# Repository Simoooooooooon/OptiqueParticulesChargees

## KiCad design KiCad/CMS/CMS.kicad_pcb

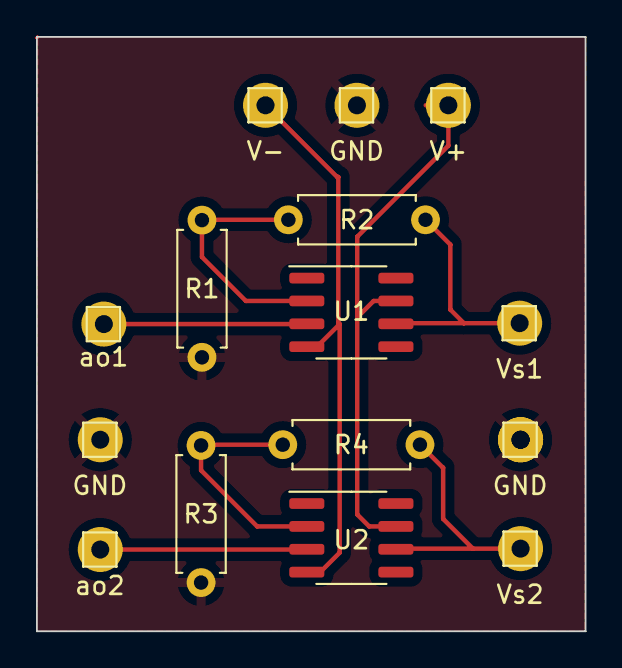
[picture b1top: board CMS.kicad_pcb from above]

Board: 2 copper layers, 30.5 x 33.0 mm, 15 parts (0 on the bottom side), 9 nets.

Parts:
GND: Conn_01x01_Pin; Pin_D0.7mm_L6.5mm_W1.8mm_FlatFork
GND#2, GND#3: Conn_01x01_Pin; Pin_D0.7mm_L6.5mm_W1.8mm_FlatFork
R1, R3: 10k; R_Axial_DIN0207_L6.3mm_D2.5mm_P7.62mm_Horizontal
R2, R4: 20k; R_Axial_DIN0207_L6.3mm_D2.5mm_P7.62mm_Horizontal
U1, U2: LTC6090; SOIC-8_3.9x4.9mm_P1.27mm
V+: Conn_01x01_Pin; Pin_D0.7mm_L6.5mm_W1.8mm_FlatFork
V-: Conn_01x01_Pin; Pin_D0.7mm_L6.5mm_W1.8mm_FlatFork
Vs1, Vs2: Conn_01x01_Pin; Pin_D0.7mm_L6.5mm_W1.8mm_FlatFork
ao1, ao2: Conn_01x01_Pin; Pin_D0.7mm_L6.5mm_W1.8mm_FlatFork

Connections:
GND: GND.1, GND#2.1, GND#3.1, R1.2, R3.2
unnamed: U1.3 (+), ao1.1
unnamed: R1.1, R2.2, U1.2 (-)
unnamed: U2.3 (+), ao2.1
unnamed: R3.1, R4.2, U2.2 (-)
unnamed: R2.1, U1.6, Vs1.1
unnamed: R4.1, U2.6, Vs2.1
V+: U1.7 (V+), U2.7 (V+), V+.1
V-: U1.4 (V-), U2.4 (V-), V-.1

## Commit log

2023-10-09 Code python pour communiquer avec la carte
    Avec read/write + multithread
2023-10-10 Add files via upload
    Un exemple simple de pilotage d'alim Instek en USB
2023-10-14 Add files via upload
    Plus besoin de multithreading -> on se sert du buffer de la carte
    Ajout de l'échantillonage
2023-10-14 Add files via upload
    Même commit, ajout du bon main
2023-10-15 Image en nuances de gris
    --> le code fonctionne pour beaucoup de valeurs mais il y a encore des soucis avec l'image obtenue (des fois simplement du noir ou du blanc et différents résultats pour une même suite d'intensités)
2023-10-17 Fixed reading
    Sampling rate is now working as I should.
2023-10-20 Moved to PyQt6 // Added a lot of try/except
2023-11-22 Add files via upload
    Un ancien projet avec la generation d'un sinal de balayage et l'affichage d'une image dans une fenetre PyQt.
2023-11-23 GenerationImageGrise
    Il y a 2 versions pour le code, sans temps et avec temps.
2023-11-24 Started the final interface
2023-11-30 Multi-threading to control the power supplies
2023-12-01 Fixes multi-threading, added quit resets.
2023-12-13 Create GenerationImage
2023-12-13 Update V1_NoShift.ui
    add connect
2023-12-14 Improved resource management
2023-12-14 Added "thread" for error messages
    Now whenever we get an error message, the interface will not freeze.
2024-01-20 Full rework
    Added sweep with NI Card
    Added image with a save option
    Added config file
    Added a progress bar
    Added customisable settings
    Added more security checks
2024-01-22 Added docstrings + fixes
2024-01-22 Uses NumPy in the Sweep.py file + added docstrings
2024-01-24 Added BMP and TIFF extensions and fixed GPP power supply quit method
2024-02-10 Added LTSpice and KiCad files
2024-02-28 Added CMS ampli
2024-03-13 Better schematics + 3D models + New images
2024-03-17 New images
2024-03-20 Reformatted the program
    Reformatted the files to better fit Python standards
2024-03-21 Separated thread, fixed VISA, added GUN and Lenses control
2024-03-22 Fixed video + reformated the code + a lot of improvements
2024-03-22 Added docstrings + improved UI + new features
2024-03-23 Added A LOT of error handling + fixed a few things
    Video improved, we get ~24 fps.
    Fixed bugs
    Usage of raised errors
2024-03-24 Added the ability to grave an image to the sample
    Needs to be cleaned up
2024-03-25 Time calculations for image printing + Docstrings + Error handling
2024-05-04 Better DRAW method overall
    Fixed a few things here and there
2024-05-06 Cleanup
2024-05-06 Fixed the help text
